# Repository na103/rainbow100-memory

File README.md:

# Rainbow 100B memory extension
this is a remake of RAM expansion board for [Digital Rainbow 100](https://en.wikipedia.org/wiki/Rainbow_100) rev B<br>

This expansion board it can reach up to 896Kb of RAM. differently to 8088 XT PCs, Rainbow 100 architecture is not limited at 640Kb of memory.<br>
Kicad schematics is derived from [Tony Duell's notes](https://github.com/na103/rainbow100-memory/blob/main/docs/Duell_ram_expansion.pdf) and at the end verified with [original DEC schematics](https://github.com/na103/rainbow100-memory/tree/main/docs/Dec).<br>
95% of the components and traces have been rebuilt respecting the original position; only the bipolar Prom E7 whos entrusted control logic for the memory banks switch has been replaced with a extra large GAL22V10.

## Bill of materials
| Qt. |    Description     |             Designator          |    Mouser Part     |             Note              |
|:---:|--------------------|---------------------------------|--------------------|-------------------------------|
|27   |Cap. 220 nF 50V     |C1 -C27                          |C430C224Z5U5TA      |                               |
|1    |Cap. 10uF 35V       |C33                              |MAL213831109E3      |                               |
|5    |Cap. 47nF 50V       |C28 - C32                        |C410C473Z5U5TA      |                               |
|2    |Cap. 10nF 50V       |C34 C35                          |C410C103Z5U5TA      |                               |
|1    |Bead Ferrite        |FB1                              |2743002112          |                               |
|1    |Rnet 9x470Ω 10 pin  |RN4                              |4610X-101-471LF     |                               |
|2    |Rnet 9x1kΩ 10 pin   |RN3 RN2                          |4610X-101-102LF     |                               |
|1    |Rnet 9x4.7kΩ 10 pin |RN1                              |4610X-AP1-472LF     |                               |
|9    |R 39Ω               |R10 - R17 R19                    |CFR-25JB-52-39R     |                               |
|1    |R 100Ω              |R18                              |CFR-25JT-52-100R    |                               |
|9    |R 47Ω               |R1 - R9                          |CFR-25JB-52-47R     |                               |
|1    |Switch DIP 4POS     |SW1                              |78RB04ST            |                               |
|1    |025X025 REC 2X30P   |J1                               |5-102766-4          |                               |
|27   |16P DIP SKT         |E1-E5 E9-E13 E17-E21 E25-E28     |1-2199298-4         |                               |
|     |                    |E33-E36 E41-E44                  |                    |                               |
|1    |24P DIP SKT         |E7                               |1-2199298-8         | optional, useful for testing  |
|1    |GAL 22V10           |E7                               |ATF22V10C-15PU      | need programmer like TL866    |
|3    |74S03N              |E8 E14 E15                       |SN74LS03N           |                               |
|1    |74LS00N             |E16                              |SN74LS00N           |                               |
|2    |74S258N             |E23 E24                          |SN74LS258N          |                               |
|1    |74LS27N             |E32                              |SN74LS27N           |                               |
|1    |74LS74AN            |E40                              |SN74LS74AN          |                               |
|2    |74LS04N             |E31 E39                          |SN74LS04N           |                               |
|1    |74S51N              |E6                               |SN74LS51N           |                               |
|1    |74LS125AN           |E22                              |SN74LS125AN         |                               |
|1    |74LS393N            |E30                              |SN74LS393N          |                               |
|1    |74LS244N            |E38                              |SN74LS244N          |                               |
|1    |74S280N             |E29                              |SN74LS280N          |                               |
|1    |74LS245N            |E37                              |SN74LS245N          |                               |
|1    |74S32N              |E45                              |SN74LS32N           |                               |
|27   |DRAM 41256-15 or    |E1-E5 E9-13 E17-E21 E25-E28      |                    | from ebay or [utsource](https://www.utsource.net)|
|     |4164-15 max 150ns   |E33-E36 E41-E44                  |                    |                               |
<br><br>
## Memory dip switch set-up

The DIP switches are to be set according to how many banks are populated and with kind of DRAM chip (256kb or 64kb).

| Dip 1-2-3-4    |    bank1     |    bank2     |    bank3     |
|:--------------:|--------------|--------------|--------------|
| off off off on |      64K     |              |              |
| off off off on |      64K     |     64K      |              |
| off off off on |      64K     |     64K      |      64K     |
| on  off off on |      256K    | 64K or empty | 64K or empty |
| on  on  off on |      256K    |     256K     | 64K or empty |
| on  on  on  on |      256K    |     256K     |      256K    |

## Building notes

due to the E7 larger size all memory banks are closer to the edge of the board, the two plastic supports need to be filed slightly to get them into their seat
<br>

<br>

If you found this my work useful, please consider buying me a cup of coffee if you want:<br>

# License

This work is licensed under a Creative Commons Attribution 4.0 International License. See [https://creativecommons.org/licenses/by/4.0/](https://creativecommons.org/licenses/by/4.0/).

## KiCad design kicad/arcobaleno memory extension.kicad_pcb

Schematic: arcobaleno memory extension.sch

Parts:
C1, C2, C3, C4, C5, C6, C7, C8, C9, C10, C11, C12, C13, C14, C15, C16, C17, C18, C19, C20, C21, C22, C23, C24, C25, C26, C27: 220nF; C_Axial_L3.8mm_D2.6mm_P7.50mm_Horizontal
C28, C29, C30, C31, C32: 47nF; C_Axial_L3.8mm_D2.6mm_P10.00mm_Horizontal
C33: 10uF; C_Axial_L12.0mm_D6.5mm_P20.00mm_Horizontal
C34, C35: 10nF; C_Axial_L3.8mm_D2.6mm_P10.00mm_Horizontal
E1, E2, E3, E4, E5, E9, E10, E11, E12, E13, E17, E18, E19, E20, E21, E25, E26, E27, E28, E33, E34, E35, E36, E41, E42, E43, E44: UPD41256C; DIP-16_W7.62mm; Manufacturer_Part_Number UPD41256C
E6: 74LS51; DIP-14_W7.62mm
E7: GAL22V10D-15LP; DIP-24_W7.62mm; Mouser Part Number 842-GAL22V10D15LP
E8, E14, E15: 74LS03; DIP-14_W7.62mm
E16: 74LS00; DIP-14_W7.62mm
E22: 74LS125; DIP-14_W7.62mm
E23, E24: 74LS258; DIP-16_W7.62mm
E29: 74LS280; DIP-14_W7.62mm
E30: 74LS393; DIP-14_W7.62mm
E31, E39: 74LS04; DIP-14_W7.62mm
E32: 74LS27; DIP-14_W7.62mm
E37: 74LS245; DIP-20_W7.62mm
E38: 74LS244; DIP-20_W7.62mm
E40: 74LS74; DIP-14_W7.62mm
E45: 74LS32; DIP-14_W7.62mm
FB1: 3 Omh 2.4 uH; L_Axial_L9.5mm_D4.0mm_P15.24mm_Horizontal_Fastron_SMCC
J1: SSW-126-01-T-D; SAMTEC_SSW-126-01-T-D; Mouser Part Number 200-SSW12601TD
R1, R2, R3, R4, R5, R6, R7, R8, R9: 47; R_Axial_DIN0207_L6.3mm_D2.5mm_P10.16mm_Horizontal
R10, R11, R12, R13, R14, R15, R16, R17, R19: 39; R_Axial_DIN0207_L6.3mm_D2.5mm_P10.16mm_Horizontal
R18: 100; R_Axial_DIN0207_L6.3mm_D2.5mm_P10.16mm_Horizontal
RN1: 4.7k; R_Array_SIP10
RN2, RN3: 1k; R_Array_SIP10
RN4: 470; R_Array_SIP10
SW1: SW_DIP_x04

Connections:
+5V: C1.2, C2.2, C3.2, C4.2, C5.2, C6.2, C7.2, C8.2, C9.2, C10.2, C11.2, C12.2, C13.2, C14.2, C15.2, C16.2, C17.2, C18.2, C19.2, C20.2, C21.2, C22.2, C23.2, C24.2, C25.2, C26.2, C27.2, C28.1, C29.1, C30.1, C31.1, C32.1, C33.1, C34.2, C35.1, E1.8 (VCC), E2.8 (VCC), E3.8 (VCC), E4.8 (VCC), E5.8 (VCC), E6.14 (VCC), E7.24 (VCC), E8.14 (VCC), E9.8 (VCC), E10.8 (VCC), E11.8 (VCC), E12.8 (VCC), E13.8 (VCC), E14.14 (VCC), E15.14 (VCC), E16.14 (VCC), E17.8 (VCC), E18.8 (VCC), E19.8 (VCC), E20.8 (VCC), E21.8 (VCC), E22.14 (VCC), E23.16 (VCC), E24.16 (VCC), E25.8 (VCC), E26.8 (VCC), E27.8 (VCC), E28.8 (VCC), E29.14 (VCC), E30.14 (VCC), E31.14 (VCC), E32.14 (VCC), E33.8 (VCC), E34.8 (VCC), E35.8 (VCC), E36.8 (VCC), E37.20 (VCC), E38.20 (VCC), E39.14 (VCC), E40.14 (VCC), E41.8 (VCC), E42.8 (VCC), E43.8 (VCC), E44.8 (VCC), E45.14 (VCC), FB1.1, FB1.2, J1.25, J1.27, J1.28, J1.35, RN1.1 (common), RN2.1 (R1.1), RN3.1 (R1.1), RN4.1 (R1.1)
/MUXA0: E23.12 (Zc), E38.18 (O0a), R17.2, RN2.3 (R2.2)
/MUXA1: E23.9 (Zd), E38.16 (O1a), R16.2, RN2.4 (R3.2)
/MUXA2: E23.4 (Za), E38.14 (O2a), R14.2, RN2.5 (R4.2)
/MUXA3: E24.4 (Za), E38.9 (O0b), R10.2, RN2.6 (R5.2)
/MUXA4: E24.12 (Zc), E38.3 (O3b), R13.2, RN2.7 (R6.2)
/MUXA5: E24.9 (Zd), E38.5 (O2b), R12.2, RN2.8 (R7.2)
/MUXA6: E23.7 (Zb), E38.12 (O3a), R15.2, RN2.9 (R8.2)
/MUXA7: E24.7 (Zb), E38.7 (O1b), R11.2, RN2.10 (R9.2)
/Rfsh0: E30.3 (Q0), E38.2 (I0a)
/Rfsh1: E30.4 (Q1), E38.4 (I1a)
/Rfsh2: E30.5 (Q2), E38.6 (I2a)
/Rfsh3: E30.6 (Q3), E30.13 (CP), E38.11 (I0b)
/Rfsh4: E30.11 (Q0), E38.17 (I3b)
/Rfsh5: E30.10 (Q1), E38.15 (I2b)
/Rfsh6: E30.9 (Q2), E38.8 (I3a)
/Rfsh7: E30.8 (Q3), E38.13 (I1b)
A0: E23.13 (I1c), J1.13
A1: E23.10 (I1d), J1.8
A2: E23.3 (I1a), J1.16
A3: E23.6 (I1b), J1.11
A4: E24.3 (I1a), J1.22
A5: E24.13 (I1c), J1.17
A6: E24.10 (I1d), J1.6
A7: E23.14 (I0c), J1.15
A8: E23.11 (I0d), J1.10
A9: E23.2 (I0a), J1.18
A10: E23.5 (I0b), J1.12
A11: E24.2 (I0a), J1.21
A12: E24.14 (I0c), J1.19
A13: E24.11 (I0d), J1.9
A14: E24.5 (I0b), J1.14
A15: E24.6 (I1b), J1.7
A16: E6.3, E7.9 (I_8), J1.47
A17: E6.5, E7.8 (I_7), J1.32
A18: E7.7 (I_6), J1.43
A19: E7.6 (I_5), J1.49, RN3.2 (R1.2)
AMUX: E6.2, E23.1 (S), E24.1 (S), E31.9, J1.20
CAS1: E1.15 (~CAS), E9.15 (~CAS), E17.15 (~CAS), E25.15 (~CAS), E26.15 (~CAS), E33.15 (~CAS), E34.15 (~CAS), E41.15 (~CAS), E42.15 (~CAS), R9.1
CAS2: E2.15 (~CAS), E3.15 (~CAS), E10.15 (~CAS), E11.15 (~CAS), E18.15 (~CAS), E19.15 (~CAS), E27.15 (~CAS), E35.15 (~CAS), E43.15 (~CAS), R2.1
CAS3: E4.15 (~CAS), E5.15 (~CAS), E12.15 (~CAS), E13.15 (~CAS), E20.15 (~CAS), E21.15 (~CAS), E28.15 (~CAS), E36.15 (~CAS), E44.15 (~CAS), R5.1
CASTime: E8.5, E8.13, E14.10, E16.4, J1.37
ClkParity: E22.8, E40.3 (C), E40.11 (C), RN3.6 (R5.2)
D0: E37.18 (B0), J1.50
D1: E37.17 (B1), J1.48
D2: E37.16 (B2), J1.46
D3: E37.15 (B3), J1.44
D4: E37.14 (B4), J1.42
D5: E37.13 (B5), J1.40
D6: E37.12 (B6), J1.38
D7: E37.11 (B7), J1.36
DRAMA0: E1.5 (A0), E2.5 (A0), E3.5 (A0), E4.5 (A0), E5.5 (A0), E9.5 (A0), E10.5 (A0), E11.5 (A0), E12.5 (A0), E13.5 (A0), E17.5 (A0), E18.5 (A0), E19.5 (A0), E20.5 (A0), E21.5 (A0), E25.5 (A0), E26.5 (A0), E27.5 (A0), E28.5 (A0), E33.5 (A0), E34.5 (A0), E35.5 (A0), E36.5 (A0), E41.5 (A0), E42.5 (A0), E43.5 (A0), E44.5 (A0), R17.1
DRAMA1: E1.7 (A1), E2.7 (A1), E3.7 (A1), E4.7 (A1), E5.7 (A1), E9.7 (A1), E10.7 (A1), E11.7 (A1), E12.7 (A1), E13.7 (A1), E17.7 (A1), E18.7 (A1), E19.7 (A1), E20.7 (A1), E21.7 (A1), E25.7 (A1), E26.7 (A1), E27.7 (A1), E28.7 (A1), E33.7 (A1), E34.7 (A1), E35.7 (A1), E36.7 (A1), E41.7 (A1), E42.7 (A1), E43.7 (A1), E44.7 (A1), R16.1
DRAMA2: E1.6 (A2), E2.6 (A2), E3.6 (A2), E4.6 (A2), E5.6 (A2), E9.6 (A2), E10.6 (A2), E11.6 (A2), E12.6 (A2), E13.6 (A2), E17.6 (A2), E18.6 (A2), E19.6 (A2), E20.6 (A2), E21.6 (A2), E25.6 (A2), E26.6 (A2), E27.6 (A2), E28.6 (A2), E33.6 (A2), E34.6 (A2), E35.6 (A2), E36.6 (A2), E41.6 (A2), E42.6 (A2), E43.6 (A2), E44.6 (A2), R14.1
DRAMA3: E1.12 (A3), E2.12 (A3), E3.12 (A3), E4.12 (A3), E5.12 (A3), E9.12 (A3), E10.12 (A3), E11.12 (A3), E12.12 (A3), E13.12 (A3), E17.12 (A3), E18.12 (A3), E19.12 (A3), E20.12 (A3), E21.12 (A3), E25.12 (A3), E26.12 (A3), E27.12 (A3), E28.12 (A3), E33.12 (A3), E34.12 (A3), E35.12 (A3), E36.12 (A3), E41.12 (A3), E42.12 (A3), E43.12 (A3), E44.12 (A3), R10.1
DRAMA4: E1.11 (A4), E2.11 (A4), E3.11 (A4), E4.11 (A4), E5.11 (A4), E9.11 (A4), E10.11 (A4), E11.11 (A4), E12.11 (A4), E13.11 (A4), E17.11 (A4), E18.11 (A4), E19.11 (A4), E20.11 (A4), E21.11 (A4), E25.11 (A4), E26.11 (A4), E27.11 (A4), E28.11 (A4), E33.11 (A4), E34.11 (A4), E35.11 (A4), E36.11 (A4), E41.11 (A4), E42.11 (A4), E43.11 (A4), E44.11 (A4), R13.1
DRAMA5: E1.10 (A5), E2.10 (A5), E3.10 (A5), E4.10 (A5), E5.10 (A5), E9.10 (A5), E10.10 (A5), E11.10 (A5), E12.10 (A5), E13.10 (A5), E17.10 (A5), E18.10 (A5), E19.10 (A5), E20.10 (A5), E21.10 (A5), E25.10 (A5), E26.10 (A5), E27.10 (A5), E28.10 (A5), E33.10 (A5), E34.10 (A5), E35.10 (A5), E36.10 (A5), E41.10 (A5), E42.10 (A5), E43.10 (A5), E44.10 (A5), R12.1
DRAMA6: E1.13 (A6), E2.13 (A6), E3.13 (A6), E4.13 (A6), E5.13 (A6), E9.13 (A6), E10.13 (A6), E11.13 (A6), E12.13 (A6), E13.13 (A6), E17.13 (A6), E18.13 (A6), E19.13 (A6), E20.13 (A6), E21.13 (A6), E25.13 (A6), E26.13 (A6), E27.13 (A6), E28.13 (A6), E33.13 (A6), E34.13 (A6), E35.13 (A6), E36.13 (A6), E41.13 (A6), E42.13 (A6), E43.13 (A6), E44.13 (A6), R15.1
DRAMA7: E1.9 (A7), E2.9 (A7), E3.9 (A7), E4.9 (A7), E5.9 (A7), E9.9 (A7), E10.9 (A7), E11.9 (A7), E12.9 (A7), E13.9 (A7), E17.9 (A7), E18.9 (A7), E19.9 (A7), E20.9 (A7), E21.9 (A7), E25.9 (A7), E26.9 (A7), E27.9 (A7), E28.9 (A7), E33.9 (A7), E34.9 (A7), E35.9 (A7), E36.9 (A7), E41.9 (A7), E42.9 (A7), E43.9 (A7), E44.9 (A7), R11.1
DRAMD0: E29.9 (B), E34.2 (DIN), E34.14 (DOUT), E35.2 (DIN), E35.14 (DOUT), E36.2 (DIN), E36.14 (DOUT), E37.2 (A0), RN1.3 (R2)
DRAMD1: E26.2 (DIN), E26.14 (DOUT), E27.2 (DIN), E27.14 (DOUT), E28.2 (DIN), E28.14 (DOUT), E29.10 (C), E37.3 (A1), RN1.4 (R3)
DRAMD2: E19.2 (DIN), E19.14 (DOUT), E20.2 (DIN), E20.14 (DOUT), E29.11 (D), E37.4 (A2), E41.2 (DIN), E41.14 (DOUT), RN1.5 (R4)
DRAMD3: E11.2 (DIN), E11.14 (DOUT), E12.2 (DIN), E12.14 (DOUT), E29.12 (E), E33.2 (DIN), E33.14 (DOUT), E37.5 (A3), RN1.6 (R5)
DRAMD4: E3.2 (DIN), E3.14 (DOUT), E4.2 (DIN), E4.14 (DOUT), E25.2 (DIN), E25.14 (DOUT), E29.13 (F), E37.6 (A4), RN1.7 (R6)
DRAMD5: E17.2 (DIN), E17.14 (DOUT), E18.2 (DIN), E18.14 (DOUT), E21.2 (DIN), E21.14 (DOUT), E29.1 (G), E37.7 (A5), RN1.8 (R7)
DRAMD6: E9.2 (DIN), E9.14 (DOUT), E10.2 (DIN), E10.14 (DOUT), E13.2 (DIN), E13.14 (DOUT), E29.2 (H), E37.8 (A6), RN1.9 (R8)
DRAMD7: E1.2 (DIN), E1.14 (DOUT), E2.2 (DIN), E2.14 (DOUT), E5.2 (DIN), E5.14 (DOUT), E29.4 (I), E37.9 (A7), RN1.10 (R9)
DRAMP: E22.3, E22.6, E32.13, E40.2 (D), E42.2 (DIN), E42.14 (DOUT), E43.2 (DIN), E43.14 (DOUT), E44.2 (DIN), E44.14 (DOUT), RN1.2 (R1)
GND: C1.1, C2.1, C3.1, C4.1, C5.1, C6.1, C7.1, C8.1, C9.1, C10.1, C11.1, C12.1, C13.1, C14.1, C15.1, C16.1, C17.1, C18.1, C19.1, C20.1, C21.1, C22.1, C23.1, C24.1, C25.1, C26.1, C27.1, C28.2, C29.2, C30.2, C31.2, C32.2, C33.2, C34.1, C35.2, E1.16 (GND), E2.16 (GND), E3.16 (GND), E4.16 (GND), E5.16 (GND), E6.7 (GND), E7.12 (GND), E8.7 (GND), E9.16 (GND), E10.16 (GND), E11.16 (GND), E12.16 (GND), E13.16 (GND), E14.7 (GND), E15.7 (GND), E16.7 (GND), E17.16 (GND), E18.16 (GND), E19.16 (GND), E20.16 (GND), E21.16 (GND), E22.7 (GND), E23.8 (GND), E24.8 (GND), E25.16 (GND), E26.16 (GND), E27.16 (GND), E28.16 (GND), E29.7 (GND), E30.7 (GND), E31.7 (GND), E32.7 (GND), E33.16 (GND), E34.16 (GND), E35.16 (GND), E36.16 (GND), E37.10 (GND), E38.10 (GND), E39.7 (GND), E40.7 (GND), E41.16 (GND), E42.16 (GND), E43.16 (GND), E44.16 (GND), E45.7 (GND), J1.1, J1.2, J1.3, J1.51, J1.52, R18.2, SW1.1, SW1.2, SW1.3, SW1.4
IO_M: E7.2 (I_1), J1.30
unnamed: E1.1 (A8), E9.1 (A8), E17.1 (A8), E25.1 (A8), E26.1 (A8), E33.1 (A8), E34.1 (A8), E41.1 (A8), E42.1 (A8), E45.8
unnamed: E6.6, R19.2, RN3.8 (R7.2)
unnamed: E8.3, R8.2, RN4.2 (R1.2)
unnamed: E8.6, R9.2, RN4.9 (R8.2)
unnamed: E8.8, R1.2, RN4.5 (R4.2)
unnamed: E8.11, R2.2, RN4.4 (R3.2)
unnamed: E2.1 (A8), E3.1 (A8), E10.1 (A8), E11.1 (A8), E18.1 (A8), E19.1 (A8), E27.1 (A8), E35.1 (A8), E43.1 (A8), E45.6
unnamed: E4.1 (A8), E5.1 (A8), E12.1 (A8), E13.1 (A8), E20.1 (A8), E21.1 (A8), E28.1 (A8), E36.1 (A8), E44.1 (A8), E45.3
unnamed: E14.3, E14.6, R4.2, RN4.7 (R6.2)
unnamed: E14.8, R5.2, RN4.8 (R7.2)
unnamed: E14.11, R6.2, RN4.10 (R9.2)
unnamed: E14.5, E14.9, E14.12, E31.4, E32.11
unnamed: E15.3, E15.6, R7.2, RN4.3 (R2.2)
unnamed: E8.2, E8.4, E15.5, E31.2, E32.9
unnamed: E8.10, E8.12, E15.9, E31.10, E32.10
unnamed: E15.8, E15.11, R3.2, RN4.6 (R5.2)
unnamed: E16.1, E22.12, E39.8
unnamed: E16.2, E39.6
unnamed: E16.3, E22.1
unnamed: E16.6, E22.9
unnamed: E16.8, E39.11
unnamed: E16.9, E16.11, E22.13
unnamed: E16.12, E39.12
unnamed: E22.2, E29.5 (Even), E32.5
unnamed: E22.5, E29.6 (Odd)
unnamed: E22.4, E22.11, RN3.5 (R4.2)
unnamed: E23.15 (OE), E24.15 (OE), E31.6
unnamed: E29.8 (A), E32.12
unnamed: E30.2 (MR), E30.12 (MR), R18.1
unnamed: E7.23 (I/O/Q_10), E31.1
unnamed: E7.16 (I/O/Q_3), E31.3
unnamed: E6.4, E31.8
unnamed: E7.22 (I/O/Q_9), E31.11
unnamed: E32.1, E39.2
unnamed: E32.4, RN3.9 (R8.2), SW1.5
unnamed: E32.6, E40.12 (D)
unnamed: E39.10, E40.1 (~R), E40.13 (~R)
unnamed: E7.5 (I_4), E45.1, RN3.7 (R6.2), SW1.6
unnamed: E45.2, E45.5, E45.9, R19.1
unnamed: E7.4 (I_3), E45.4, RN3.4 (R3.2), SW1.7
unnamed: E7.3 (I_2), E45.10, RN3.3 (R2.2), SW1.8
PUI: E14.1, E15.1, E15.13, E40.4 (~S), E40.10 (~S), RN2.2 (R1.2)
ParityCtrl: E39.9, J1.24
ParityOut: E40.5 (Q), J1.5
RAS1: E1.4 (~RAS), E9.4 (~RAS), E17.4 (~RAS), E25.4 (~RAS), E26.4 (~RAS), E33.4 (~RAS), E34.4 (~RAS), E41.4 (~RAS), E42.4 (~RAS), R7.1
RAS2: E2.4 (~RAS), E3.4 (~RAS), E10.4 (~RAS), E11.4 (~RAS), E18.4 (~RAS), E19.4 (~RAS), E27.4 (~RAS), E35.4 (~RAS), E43.4 (~RAS), R3.1
RAS3: E4.4 (~RAS), E5.4 (~RAS), E12.4 (~RAS), E13.4 (~RAS), E20.4 (~RAS), E21.4 (~RAS), E28.4 (~RAS), E36.4 (~RAS), E44.4 (~RAS), R4.1
RASTime: E14.4, E15.4, E15.10, J1.4
RD: E16.5, E39.1, J1.41
RfshInc: E30.1 (CP), J1.33
RfshRAS: E14.2, E15.2, E15.12, J1.23
WR: E8.1, E8.9, E14.13, E16.13, J1.45
WR1: E1.3 (~WE), E9.3 (~WE), E17.3 (~WE), E25.3 (~WE), E26.3 (~WE), E33.3 (~WE), E34.3 (~WE), E41.3 (~WE), E42.3 (~WE), R8.1
WR2: E2.3 (~WE), E3.3 (~WE), E10.3 (~WE), E11.3 (~WE), E18.3 (~WE), E19.3 (~WE), E27.3 (~WE), E35.3 (~WE), E43.3 (~WE), R1.1
WR3: E4.3 (~WE), E5.3 (~WE), E12.3 (~WE), E13.3 (~WE), E20.3 (~WE), E21.3 (~WE), E28.3 (~WE), E36.3 (~WE), E44.3 (~WE), R6.1
_BuffEn: E22.10, E32.2, E32.3, E32.8, E37.19 (CE), E39.13
_DT_R: E37.1 (A->B), E39.5, J1.39
_NMI: E40.8 (~Q), J1.26
_RST: E16.10, J1.34
_RfshAddr: E31.5, E38.1 (OEa), E38.19 (OEb), J1.31

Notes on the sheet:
Refresh Counter
BANK SELECT
Data Buffer and Parity
BankEn1
BankEn2
BankEn3
When the PC 100-B memory extension option is installed, address bit 18 is used in conjunction with address bits 16, 17, and 19 to select the memory stack.
The status of this input signal determines which set of four signals are used to select the memory banks in the PC100-A or PC100-B memory extension options. If a PC100-A memory option is installed, the signal is ground. If a PC 100-B memory option is installed, this signal is high.
When a PC 100-A memory option is installed, NONSHRCYC is asserted low cycle to enable memory option accesses. When a PC 100-B memory option is installed, the 8088 processor asserts 10/M low to enable memory option accesses.
BANK ENABLE
BANK 1
BANK 2
BANK 3
The switch labeled '4' is easy. It must always be ON. Switches 1 through 3 correspond to memory banks 1 through 3, respectively. If a memory bank contains 256k chips, then the corresponding switch must be ON. Likewise, if a memory bank contains 64k chips, the corresponding switch must be OFF. If a 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
BANK1
BANK2
BANK3
RAM Address

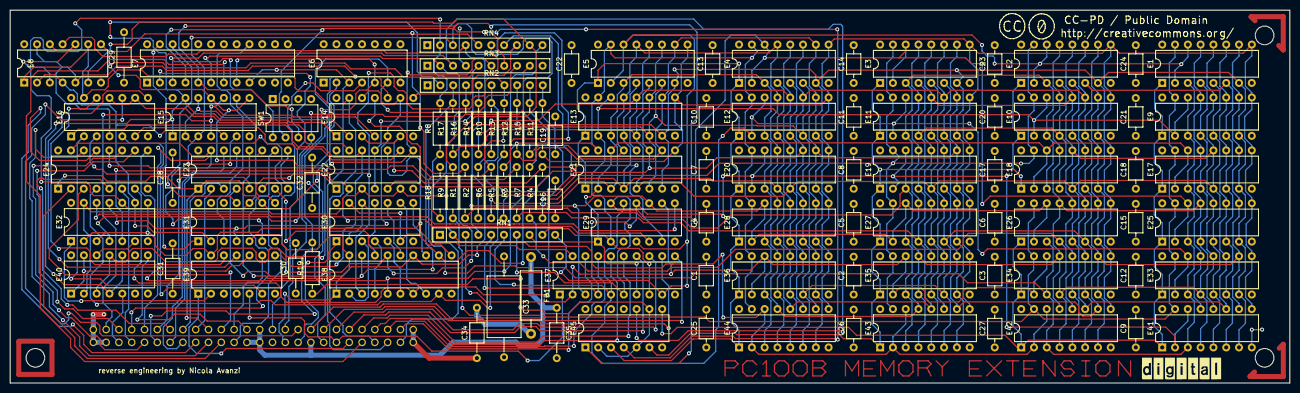
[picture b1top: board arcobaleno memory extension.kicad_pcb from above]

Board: 4 copper layers, 254.0 x 74.0 mm, 106 parts (1 on the bottom side), 130 nets.

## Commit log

2023-01-17 Update LICENSE
2023-01-17 Duell and DEC schematics
2023-01-17 Kicad project with gerber
2023-01-17 mem map truth table
2023-01-17 pld and jed
2023-01-17 switch and ram setup
2023-01-18 plastic stand
2024-03-29 PC100 memory util prg
    BL-T905A-BV
    PC100 MEMORY UTIL PRG RX50
